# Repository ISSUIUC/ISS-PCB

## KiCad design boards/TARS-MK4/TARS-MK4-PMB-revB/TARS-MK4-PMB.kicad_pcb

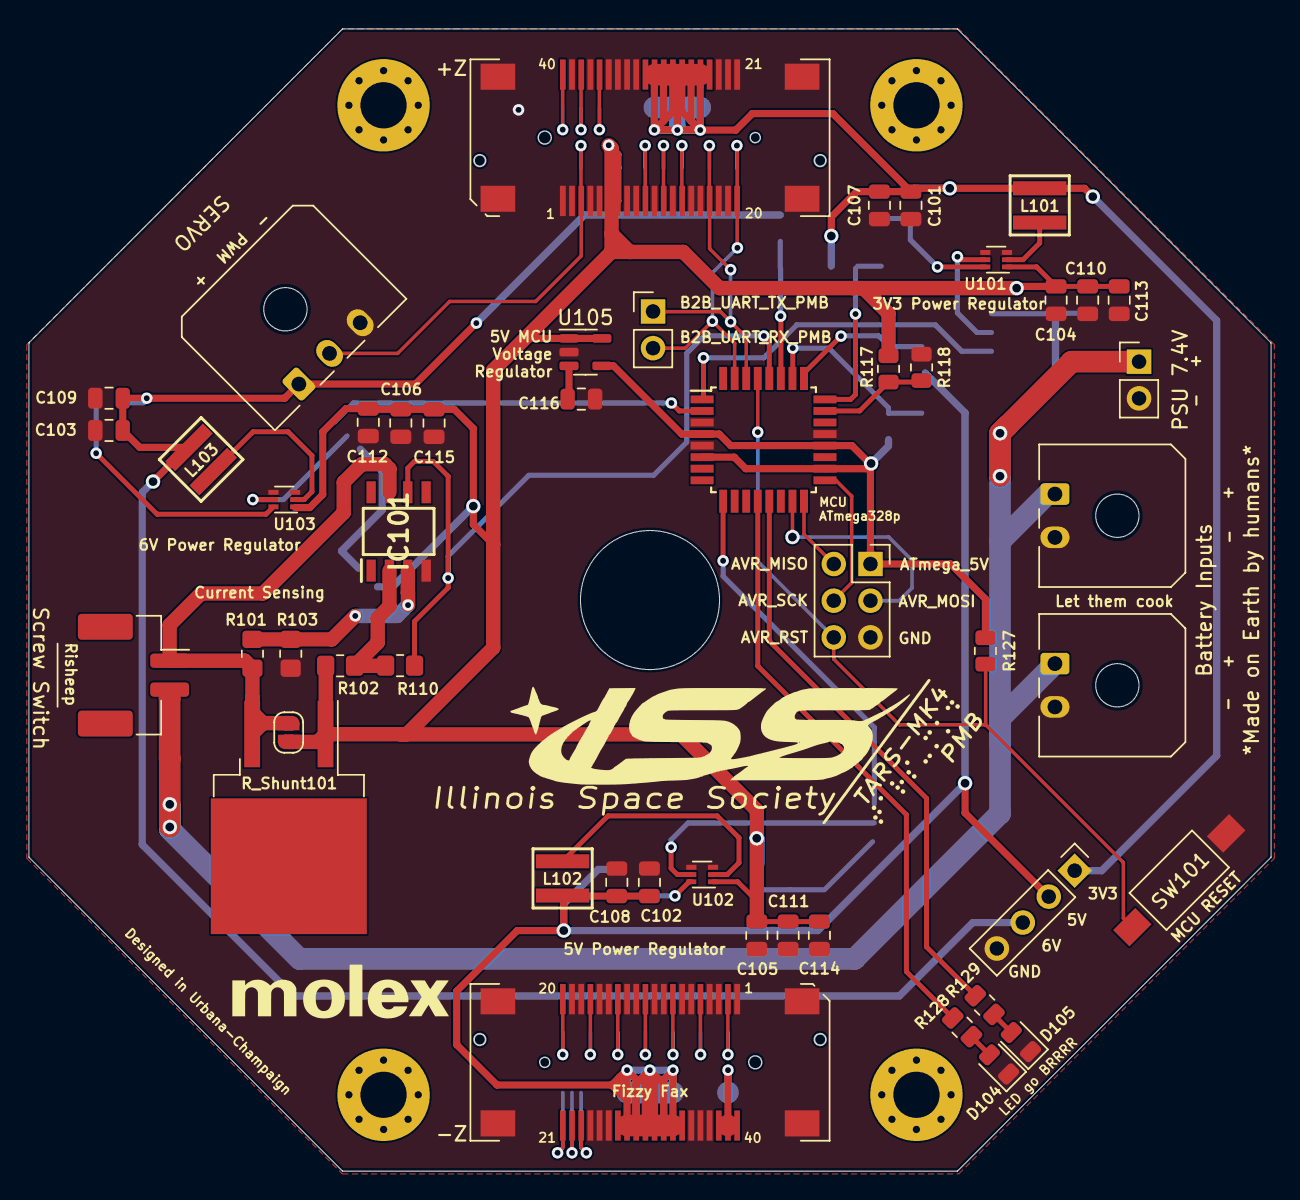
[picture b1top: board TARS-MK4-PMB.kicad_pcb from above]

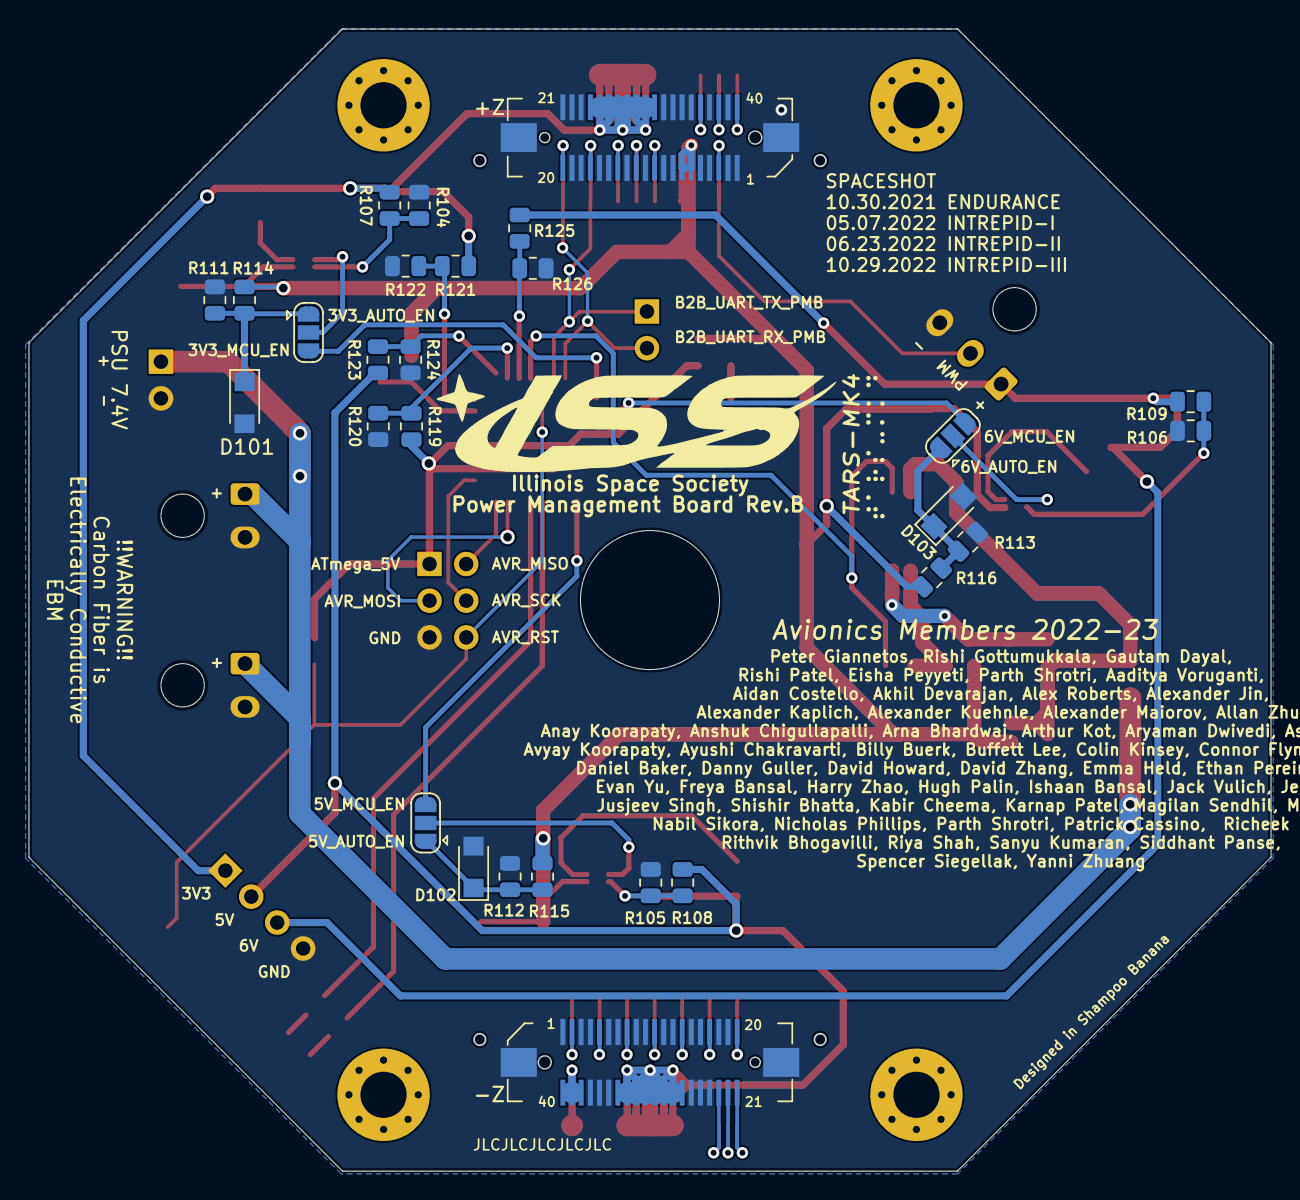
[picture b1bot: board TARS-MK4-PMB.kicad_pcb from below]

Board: 2 copper layers, 86.0 x 79.1 mm, 77 parts (28 on the bottom side), 60 nets.

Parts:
C101, C102, C103, C107, C108, C109: 22 uF; C_0805_2012Metric
C104, C105, C106, C110, C111, C112: 10uF; C_0805_2012Metric
C113, C114, C115, C116: 0.1uF; C_0805_2012Metric
D101, D102, D103: D_Zener; D_SMF
D104: GREEN; LED_0805_2012Metric
D105: ORANGE; LED_0805_2012Metric
IC101: LT1001CS8#PBF; LT1001-CS8
J101: Molex Micro-Lock 5055780271; Molex_CLIK-Mate_502494-0270_1x02-1MP_P2.00mm_Horizontal
J102, J103: Molex Micro-Fit 436500200; Molex_Micro-Fit_3.0_43650-0200_1x02_P3.00mm_Horizontal
J104: Molex Micro-Fit 436500300; Molex_Micro-Fit_3.0_43650-0300_1x03_P3.00mm_Horizontal
J105, J109: Conn_01x02; PinHeader_1x02_P2.54mm_Vertical
J106: Molex_SlimStack_2091680401_2x20_P0.635mm
J107: Molex_SlimStack_2091680401_2x20_P0.635mm; Molex_SlimStack_Receptacle_2091680401_2x20_P0.635mm
J108: Conn_01x04; PinHeader_1x04_P2.54mm_Vertical
J110, J111: Molex_SlimStack_Plug_2x20_P0.365mm; Molex_SlimStack_Plug_536470474_2x20_P0.365mm
J112: AVRISP; PinSocket_2x03_P2.54mm_Vertical
JP101: Jumper_2_Open; SolderJumper-2_P1.3mm_Open_RoundedPad1.0x1.5mm
JP102, JP103, JP104: SolderJumper_3_Open; SolderJumper-3_P1.3mm_Open_RoundedPad1.0x1.5mm
L101: 1.5 uH; 1.5_74438356015
L102: 1.8 uH; 1.8_74438356018
L103: 2.2 uH; 2.2_74438356022
R101, R102: 1K; R_0805_2012Metric_Pad1.20x1.40mm_HandSolder
R103, R110: 5K; R_0805_2012Metric_Pad1.20x1.40mm_HandSolder
R104, R105, R106, R111, R112, R113: 30k; R_0805_2012Metric
R107: 135k; R_0805_2012Metric
R108: 220k; R_0805_2012Metric
R109: 270k; R_0805_2012Metric
R114, R115, R116: 20k; R_0805_2012Metric
R117: 200k; R_0805_2012Metric
R118, R119, R120, R121, R122, R123, R124, R125, R126: 100k; R_0805_2012Metric
R127: 10k; R_0805_2012Metric
R128, R129: 150; R_0805_2012Metric
R_Shunt101: 0.1; TO-263-2_TabPin1
SW101: SW_Push; SW_SPST_FSMSM
U101, U102, U103: TI_TPS564247DRLR; SOT-563
U104: ATmega328P-A; TQFP-32_7x7mm_P0.8mm
U105: LK112M50TR; SOT-23-5

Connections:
/3V3: C101.1, C107.1, J106.24, J106.25, J106.26, J106.27, J106.28, J106.29, J106.30, J106.31, J108.1, J110.24, J110.25, J110.26, J110.27, J110.28, J110.29, J110.30, J110.31, L101.1, R107.2, R121.1
/3V3_EN: JP102.3 (B), U104.1 (PD3)
/3V3_SENSE: R121.2, R122.1, U104.24 (PC1)
/5V: C102.1, C108.1, J107.27, J107.28, J107.29, J107.30, J107.31, J107.32, J107.33, J107.34, J108.2, J111.27, J111.28, J111.29, J111.30, J111.31, J111.32, J111.33, J111.34, L102.1, R108.2, R123.1
/5V_EN: JP103.3 (B), U104.9 (PD5)
/5V_MCU_SENSE: R119.2, R120.1, U104.26 (PC3)
/5V_SENSE: R123.2, R124.1, U104.25 (PC2)
/6V: C103.1, C109.1, J104.1, J108.3, L103.1, R109.2, R125.1
/6V_EN: JP104.3 (B), U104.2 (PD4)
/6V_SENSE: R125.2, R126.1, U104.27 (PC4)
/ATmega_5V: J112.1, R119.1, R127.1, U104.4 (VCC), U104.6 (VCC), U104.18 (AVCC), U104.20 (AREF), U105.4 (OUT)
/AVR_MISO: J112.2, U104.16 (PB4)
/AVR_MOSI: J112.3, U104.15 (PB3)
/AVR_RST: J112.6, R127.2, SW101.1, U104.29 (~RESET/PC6)
/AVR_SCK: J112.4, U104.17 (PB5)
/B2B_I2C_SCL: J107.11, J111.11
/B2B_I2C_SDA: J107.8, J111.8
/B2B_RFM96W_CS: J107.22, J111.22
/B2B_RFM96W_INT: J107.23, J111.23
/B2B_RFM96W_RESET: J107.21, J111.21
/B2B_SERVO_PWM: J104.2, J106.3, J110.3
/B2B_SPI_MISO: J107.20, J111.20
/B2B_SPI_MOSI: J107.5, J111.5
/B2B_SPI_SCK: J107.2, J111.2
/B2B_UART_RX_PMB: J106.20, J109.2, J110.20, U104.31 (PD1)
/B2B_UART_RX_TELEM: J107.17, J111.17
/B2B_UART_TX_PMB: J106.17, J109.1, J110.17, U104.30 (PD0)
/B2B_UART_TX_TELEM: J107.14, J111.14
/LED_GREEN: R128.1, U104.12 (PB0)
/LED_ORANGE: R129.1, U104.13 (PB1)
/PSU_RAW: J101.2, J102.1, J103.1, J105.1
/RESERVED_1: J106.10, J110.10
/RESERVED_2: J106.12, J110.12
/RESERVED_3: J106.36, J110.36
/RESERVED_4: J106.38, J110.38
/TEENSY_GPIO_1: J106.40, J110.40
/TEENSY_SWITCH: J106.14, J110.14
/Teensy_3V3: J107.38, J107.39, J107.40, J111.38, J111.39, J111.40
/VBAT: C104.1, C105.1, C106.1, C110.1, C111.1, C112.1, C113.1, C114.1, C115.1, J106.6, J106.7, J110.6, J110.7, JP101.1 (A), R102.1, R114.2, R115.2, R116.2, R117.1, R_Shunt101.1, U101.1 (VIN), U102.1 (VIN), U103.1 (VIN), U105.1 (SHDN), U105.5 (IN)
/VBAT_CURRENT_SENSE: IC101.6 (OUT), R110.1, U104.28 (PC5)
/VBAT_RAW: IC101.7 (V+), J101.1, JP101.2 (B), R101.1, R_Shunt101.2
/VBAT_SENSE: R117.2, R118.1, U104.23 (PC0)
GND: C101.2, C102.2, C103.2, C104.2, C105.2, C106.2, C107.2, C108.2, C109.2, C110.2, C111.2, C112.2, C113.2, C114.2, C115.2, C116.2, D101.2 (A), D102.2 (A), D103.2 (A), D104.1 (K), D105.1 (K), IC101.4 (V-), J102.2, J103.2, J104.3, J105.2, J106.1, J106.2, J106.4, J106.5, J106.8, J106.9, J106.11, J106.13, J106.15, J106.16, J106.18, J106.19, J106.21, J106.22, J106.23, J106.32, J106.33, J106.34, J106.35, J106.37, J106.39, J106.GND, J107.1, J107.3, J107.4, J107.6, J107.7, J107.9, J107.10, J107.12, J107.13, J107.15, J107.16, J107.18, J107.19, J107.24, J107.25, J107.26, J107.35, J107.36, J107.37, J107.GND, J108.4, J110.1, J110.2, J110.4, J110.5, J110.8, J110.9, J110.11, J110.13, J110.15, J110.16, J110.18, J110.19, J110.21, J110.22, J110.23, J110.32, J110.33, J110.34, J110.35, J110.37, J110.39, J110.GND, J111.1, J111.3, J111.4, J111.6, J111.7, J111.9, J111.10, J111.12, J111.13, J111.15, J111.16, J111.18, J111.19, J111.24, J111.25, J111.26, J111.35, J111.36, J111.37, J111.GND, J112.5, R103.1, R104.2, R105.2, R106.2, R111.2, R112.2, R113.2, R118.2, R120.2, R122.2, R124.2, R126.2, SW101.2, U101.3 (GND), U101.4 (AGND), U102.3 (GND), U102.4 (AGND), U103.3 (GND), U103.4 (AGND), U104.3 (GND), U104.5 (GND), U104.21 (GND), U105.2 (GND)
unnamed: C116.1, U105.3 (Bypass)
unnamed: D101.1 (K), JP102.1 (A), R111.1, R114.1
unnamed: D102.1 (K), JP103.1 (A), R112.1, R115.1
unnamed: D103.1 (K), JP104.1 (A), R113.1, R116.1
unnamed: D104.2 (A), R128.2
unnamed: D105.2 (A), R129.2
unnamed: IC101.2 (-IN), R102.2, R110.2
unnamed: IC101.3 (+IN), R101.2, R103.2
unnamed: JP102.2 (C), U101.5 (EN)
unnamed: JP103.2 (C), U102.5 (EN)
unnamed: JP104.2 (C), U103.5 (EN)
unnamed: L101.2, U101.2 (SW)
unnamed: L102.2, U102.2 (SW)
unnamed: L103.2, U103.2 (SW)
unnamed: R104.1, R107.1, U101.6 (FB)
unnamed: R105.1, R108.1, U102.6 (FB)
unnamed: R106.1, R109.1, U103.6 (FB)

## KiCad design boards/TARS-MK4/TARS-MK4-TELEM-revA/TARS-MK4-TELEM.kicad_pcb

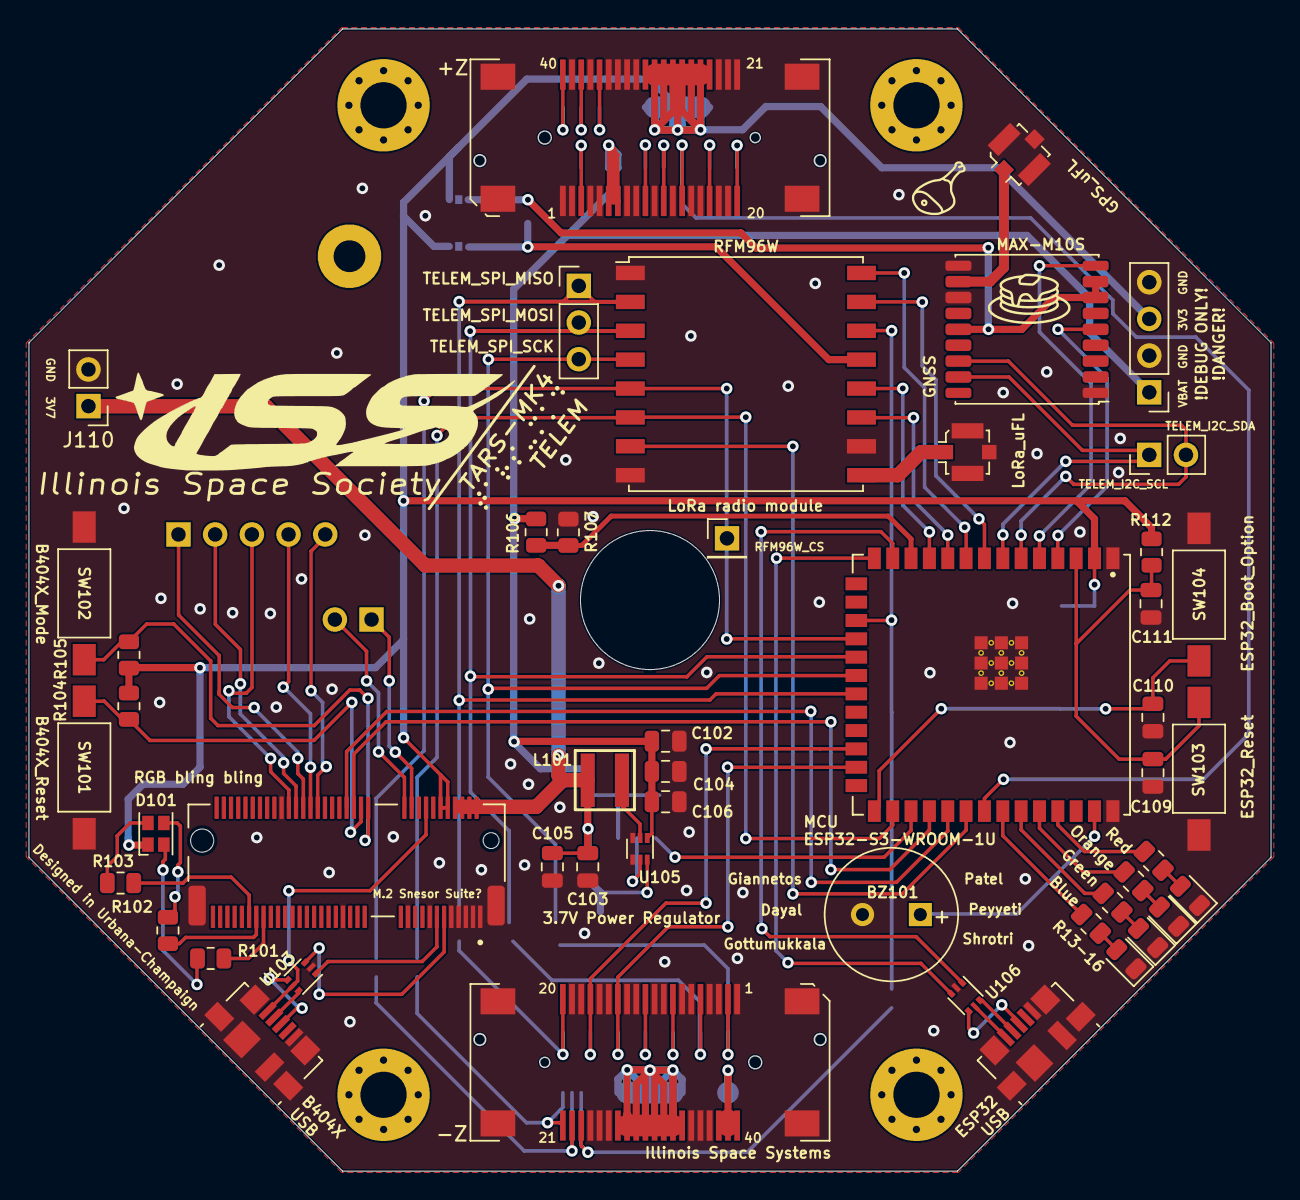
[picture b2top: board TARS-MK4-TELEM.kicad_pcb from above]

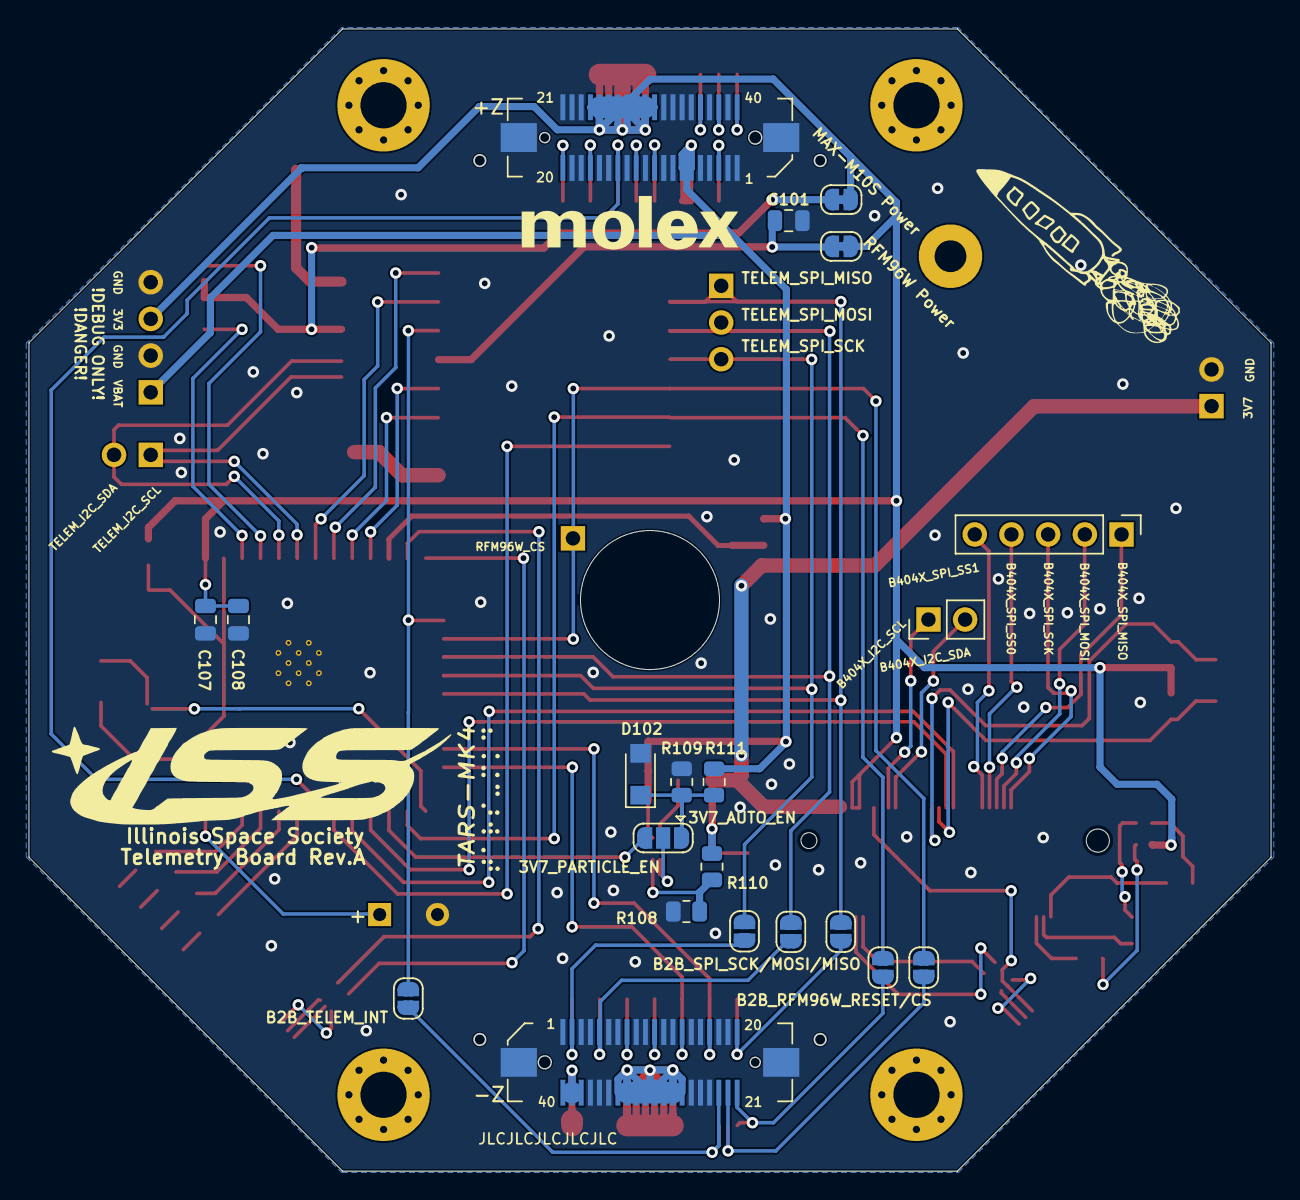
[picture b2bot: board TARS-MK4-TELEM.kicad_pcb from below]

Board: 2 copper layers, 86.0 x 79.1 mm, 70 parts (21 on the bottom side), 88 nets.

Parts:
BZ101: Buzzer; MagneticBuzzer_PUI_AT-0927-TT-6-R
C101, C102, C104: 10uF; C_0805_2012Metric
C103, C105, C107: 22uF; C_0805_2012Metric
C106, C108, C109, C110: 0.1uF; C_0805_2012Metric
C111: 1uF; C_0805_2012Metric
D101: LED_ABGR; LED_Cree-PLCC4_2x2mm_CW
D102: PTZTFTE255.1B; D_SMF
D103: RED LED; LED_0805_2012Metric
D104: ORANGE LED; LED_0805_2012Metric
D105: GREEN LED; LED_0805_2012Metric
D106: BLUE LED; LED_0805_2012Metric
J101, J104: U.FL; U.FL_Molex_MCRF_73412-0110_Vertical
J102: B404X; TE_21992304
J103, J107: USB_B_Micro; USB_Micro-B_Molex_47346-0001
J105: Conn_01x04; PinHeader_1x05_P2.54mm_Vertical
J106, J110, J115: Conn_01x02; PinHeader_1x02_P2.54mm_Vertical
J108, J109: Molex_SlimStack_2091680401_2x20_P0.635mm
J111: Conn_01x04; PinHeader_1x04_P2.54mm_Vertical
J112, J113: Molex_SlimStack_Plug_2x20_P0.365mm
J114: Conn_01x03; PinHeader_1x03_P2.54mm_Vertical
J116: Conn_01x05; PinHeader_1x01_P2.54mm_Vertical
JP101, JP102, JP103, JP104, JP105, JP108: SolderJumper_2_Open; SolderJumper-2_P1.3mm_Open_RoundedPad1.0x1.5mm
JP106, JP107: Jumper_NC_Small; SolderJumper-2_P1.3mm_Bridged_RoundedPad1.0x1.5mm
JP109: SolderJumper_3_Open; SolderJumper-3_P1.3mm_Open_RoundedPad1.0x1.5mm
L101: 1.8uH; 1.8_74438356018
R101, R102, R103: 1K; R_0805_2012Metric
R104, R105: 9K; R_0805_2012Metric
R106: 200k; R_0805_2012Metric
R107: 100k; R_0805_2012Metric
R108, R109: 30k; R_0805_2012Metric
R110: 155k; R_0805_2012Metric
R111: 20k; R_0805_2012Metric
R112: 10K; R_0805_2012Metric
R113, R114, R115, R116: 470; R_0805_2012Metric
SW101, SW102, SW103, SW104: SW_Push; SW_SPST_FSMSM
U101: MAX-M10S; ublox_MAX
U102: RFM96W-433S2; HOPERF_RFM9XW_SMD
U103, U106: USBLC6-2P6; SOT-666
U104: ESP32-S3-WROOM-1U
U105: TI_TPS564247DRLR; SOT-563

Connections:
/3V3: C107.1, C108.1, D101.1 (A), J102.10, J102.12, J108.24, J108.25, J108.26, J108.27, J108.28, J108.29, J108.30, J108.31, J111.3, J112.24, J112.25, J112.26, J112.27, J112.28, J112.29, J112.30, J112.31, JP106.1 (A), JP107.1 (A), R104.1, R105.1, R112.2, U104.2 (3V3)
/3V7: C103.1, C105.1, J102.2, J102.4, J102.6, J102.8, J110.1, L101.1, R110.2
/3V7_PARTICLE_EN: JP109.3 (B), U104.29 (IO36)
/5V: J109.27, J109.28, J109.29, J109.30, J109.31, J109.32, J109.33, J109.34, J113.27, J113.28, J113.29, J113.30, J113.31, J113.32, J113.33, J113.34
/B2B_I2C_SCL: J109.11, J113.11
/B2B_I2C_SDA: J109.8, J113.8
/B2B_RFM96W_CS: J109.22, J113.22, JP102.1 (A)
/B2B_RFM96W_INT: J109.23, J113.23, JP108.2 (B)
/B2B_RFM96W_RESET: J109.21, J113.21, JP101.1 (A)
/B2B_SERVO_PWM: J108.3, J112.3
/B2B_SPI_MISO: J109.20, J113.20, JP103.1 (A)
/B2B_SPI_MOSI: J109.5, J113.5, JP104.1 (A)
/B2B_SPI_SCK: J109.2, J113.2, JP105.1 (A)
/B2B_UART_RX_PMB: J108.20, J112.20
/B2B_UART_RX_TELEM: J109.17, J113.17, U104.24 (IO47)
/B2B_UART_TX_PMB: J108.17, J112.17
/B2B_UART_TX_TELEM: J109.14, J113.14, U104.25 (IO48)
/B404X_I2C_SCL: J102.20, J106.1
/B404X_I2C_SDA: J102.22, J106.2
/B404X_Mode: J102.32, R105.2, SW102.2
/B404X_Reset: J102.34, R104.2, SW101.2
/B404X_SPI_MISO: J102.50, J105.1
/B404X_SPI_MOSI: J102.52, J105.2
/B404X_SPI_SCK: J102.54, J105.3
/B404X_SPI_SS0: J102.48, J105.4
/B404X_SPI_SS1: J102.46, J105.5
/CHIP_PU: C109.2, C111.1, R112.1, SW103.2, U104.3 (EN)
/ESP_USB_DN: U104.13 (IO19), U106.1 (I/O1)
/ESP_USB_DP: U104.14 (IO20), U106.3 (I/O2)
/GPIO_0: C110.2, SW104.2, U104.27 (IO0)
/LED_BLUE: R116.1, U104.34 (IO41)
/LED_GREEN: R115.1, U104.35 (IO42)
/LED_ORANGE: R114.1, U104.36 (RXD0)
/LED_RED: R113.1, U104.37 (TXD0)
/LTE_USB_5V: J102.16, J103.1 (VBUS), U103.5 (VBUS)
/LTE_USB_DN: J102.13, U103.1 (I/O1)
/LTE_USB_DP: J102.11, U103.3 (I/O2)
/MAX-M10S_INT: U101.5 (EXTINT), U104.4 (IO4)
/MAX-M10S_RESET: U101.9 (RESET_N), U104.5 (IO5)
/PWM_BUZZER: BZ101.1 (-), U104.39 (IO1)
/RESERVED_1: J108.10, J112.10
/RESERVED_2: J108.12, J112.12
/RESERVED_3: J108.36, J112.36
/RESERVED_4: J108.38, J112.38
/RFM96W_CS: J116.1, JP102.2 (B), U102.5 (NSS), U104.18 (IO10)
/RFM96W_DIO1: U102.15 (DIO1), U104.8 (IO15)
/RFM96W_DIO2: U102.16 (DIO2), U104.9 (IO16)
/RFM96W_DIO3: U102.11 (DIO3), U104.10 (IO17)
/RFM96W_DIO4: U102.12 (DIO4), U104.11 (IO18)
/RFM96W_DIO5: U102.7 (DIO5), U104.32 (IO39)
/RFM96W_RESET: JP101.2 (B), U102.6 (RESET), U104.28 (IO35)
/RGB_B: J102.65, R103.1
/RGB_G: J102.63, R102.1
/RGB_R: J102.61, R101.1
/TEENSY_GPIO_1: J108.40, J112.40
/TEENSY_SWITCH: J108.14, J112.14, U104.33 (IO40)
/TELEM_I2C_SCL: J115.1, U101.17 (SCL), U104.7 (IO7)
/TELEM_I2C_SDA: J115.2, U101.16 (SDA), U104.6 (IO6)
/TELEM_INT: JP108.1 (A), U102.14 (DIO0), U104.17 (IO9)
/TELEM_SPI_MISO: J114.1, JP103.2 (B), U102.2 (MISO), U104.21 (IO13)
/TELEM_SPI_MOSI: J114.2, JP104.2 (B), U102.3 (MOSI), U104.19 (IO11)
/TELEM_SPI_SCK: J114.3, JP105.2 (B), U102.4 (SCK), U104.20 (IO12)
/Teensy_3V3: J109.38, J109.39, J109.40, J113.38, J113.39, J113.40
/UART_RX_PARTICLE: J102.38, U104.31 (IO38)
/UART_TX_PARTICLE: J102.36, U104.30 (IO37)
/VBAT: C102.1, C104.1, C106.1, J108.6, J108.7, J111.1, J112.6, J112.7, R106.1, R111.2, U105.1 (VIN)
/VBAT_SENSE: R106.2, R107.1, U104.12 (IO8)
GND: BZ101.2 (+), C101.2, C102.2, C103.2, C104.2, C105.2, C106.2, C107.2, C108.2, C109.1, C110.1, C111.2, D102.2 (A), D103.1 (K), D104.1 (K), D105.1 (K), D106.1 (K), J101.2 (Ext), J102.1, J102.3, J102.5, J102.7, J102.9, J102.15, J102.21, J102.39, J102.56, J102.S1 (SHIELD), J103.5 (GND), J103.6 (Shield), J104.2 (Ext), J107.5 (GND), J107.6 (Shield), J108.1, J108.2, J108.4, J108.5, J108.8, J108.9, J108.11, J108.13, J108.15, J108.16, J108.18, J108.19, J108.21, J108.22, J108.23, J108.32, J108.33, J108.34, J108.35, J108.37, J108.39, J108.GND, J109.1, J109.3, J109.4, J109.6, J109.7, J109.9, J109.10, J109.12, J109.13, J109.15, J109.16, J109.18, J109.19, J109.24, J109.25, J109.26, J109.35, J109.36, J109.37, J109.GND, J110.2, J111.2, J111.4, J112.1, J112.2, J112.4, J112.5, J112.8, J112.9, J112.11, J112.13, J112.15, J112.16, J112.18, J112.19, J112.21, J112.22, J112.23, J112.32, J112.33, J112.34, J112.35, J112.37, J112.39, J112.GND, J113.1, J113.3, J113.4, J113.6, J113.7, J113.9, J113.10, J113.12, J113.13, J113.15, J113.16, J113.18, J113.19, J113.24, J113.25, J113.26, J113.35, J113.36, J113.37, J113.GND, R107.2, R108.2, R109.2, SW101.1, SW102.1, SW103.1, SW104.1, U101.1 (GND), U101.10 (GND), U101.12 (GND), U102.1 (GND), U102.8 (GND), U102.10 (GND), U103.2 (GND), U104.1 (GND), U104.40 (GND), U104.41 (EPAD), U105.3 (GND), U105.4 (AGND), U106.2 (GND)
unnamed: C101.1, JP106.2 (B), U102.13 (3.3V)
unnamed: D101.2 (BK), R103.2
unnamed: D101.3 (GK), R102.2
unnamed: D101.4 (RK), R101.2
unnamed: D102.1 (K), JP109.1 (A), R109.1, R111.1
unnamed: D103.2 (A), R113.2
unnamed: D104.2 (A), R114.2
unnamed: D105.2 (A), R115.2
unnamed: D106.2 (A), R116.2
unnamed: J101.1 (In), U101.11 (RF_IN)
unnamed: J103.2 (D-), U103.6 (I/O1)
unnamed: J103.3 (D+), U103.4 (I/O2)
unnamed: J104.1 (In), U102.9 (ANT)
unnamed: J107.1 (VBUS), U106.5 (VBUS)
unnamed: J107.2 (D-), U106.6 (I/O1)
unnamed: J107.3 (D+), U106.4 (I/O2)
unnamed: JP107.2 (B), U101.7 (V_IO), U101.8 (VCC), U101.14 (VCC_RF)
unnamed: JP109.2 (C), U105.5 (EN)
unnamed: L101.2, U105.2 (SW)
unnamed: R108.1, R110.1, U105.6 (FB)
